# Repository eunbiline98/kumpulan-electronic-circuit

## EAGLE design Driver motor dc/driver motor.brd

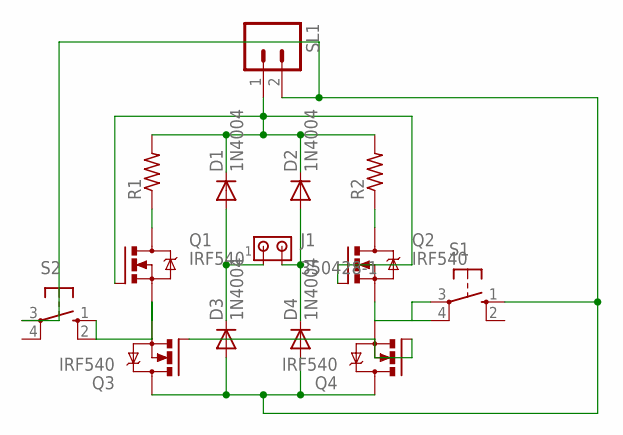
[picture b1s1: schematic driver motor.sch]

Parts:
D1, D2, D3, D4: 1N4004; DO41-10
J1: 350428-1
Q1, Q2, Q3, Q4: IRF540; TO220BV
R1, R2: R-US_0207/7; 0207/7
S1, S2: 10-XX; B3F-10XX
SL1: M02; 02P

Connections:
unnamed: D1.C, D2.C, Q1.G, Q2.G, R1.2, R2.2, SL1.1
unnamed: D1.A, D3.C, J1.1
unnamed: D2.A, D4.C, J1.2
unnamed: D3.A, D4.A, Q3.D, Q4.D, S1.1 (S), S2.3, SL1.2
unnamed: Q3.G, Q4.G
unnamed: Q2.S, Q4.S, S1.3, S1.4 (P1)
unnamed: Q1.D, R1.1
unnamed: Q2.D, R2.1
unnamed: Q1.S, Q3.S, S2.1 (S), S2.2 (S1)

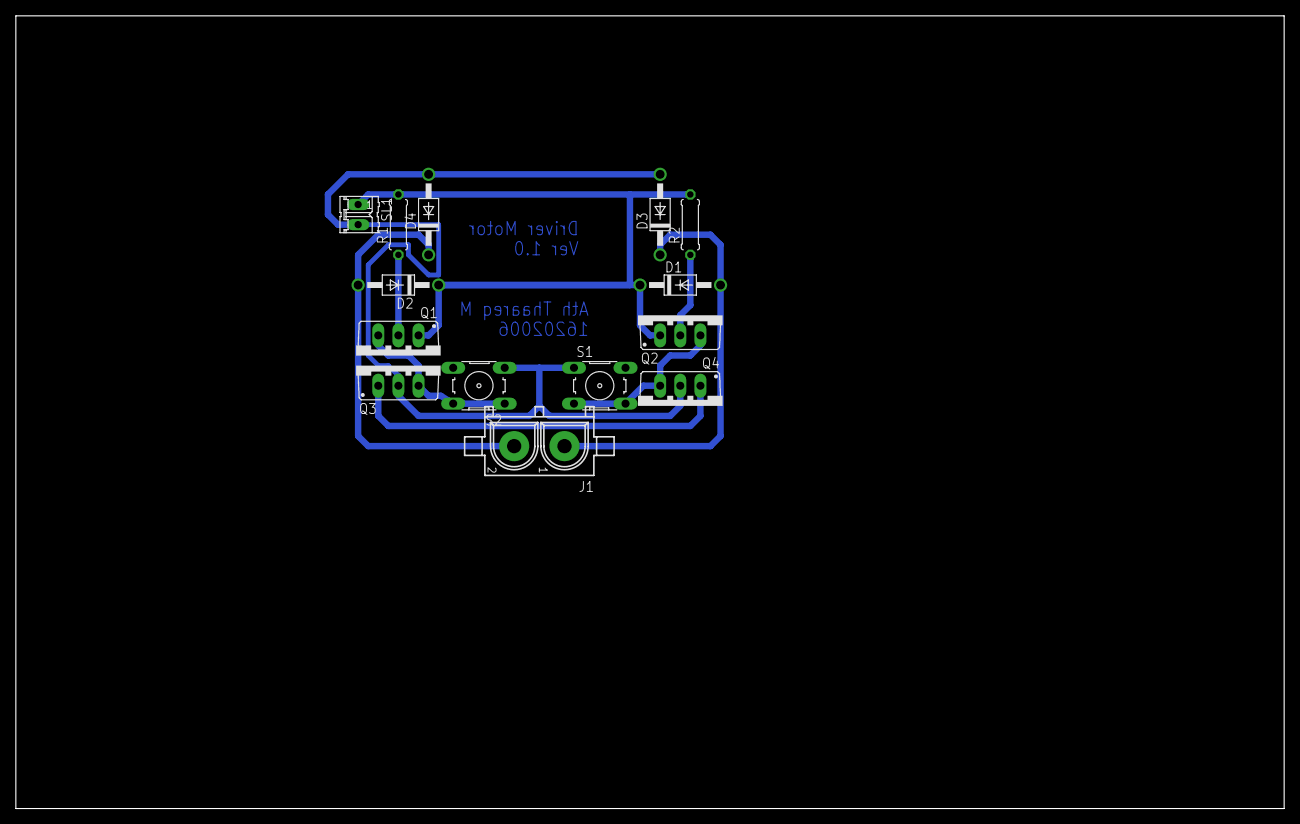
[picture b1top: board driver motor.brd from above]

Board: 2 copper layers, 160.0 x 100.0 mm, 14 parts (0 on the bottom side), 9 nets.

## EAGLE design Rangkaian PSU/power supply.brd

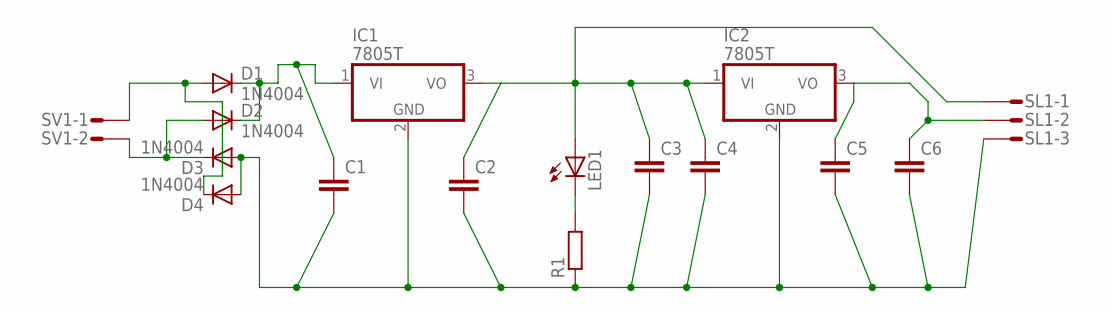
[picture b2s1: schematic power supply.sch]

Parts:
C1, C2, C3, C4, C5, C6: C5/5.5; C5B5.5
D1, D2, D3, D4: 1N4004; DO41-10
IC1, IC2: 7805T; TO220H
LED1: LED5MM
R1: R-EU_0207/7; 0207/7
SL1: M03S; 03P
SV1: L02P

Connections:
unnamed: C1.1, D1.C, D2.C, IC1.1 (VI)
unnamed: C1.2, C2.2, C3.2, C4.2, C5.2, C6.2, D3.A, D4.A, IC1.2 (GND), IC2.2 (GND), R1.1, SL1.3
unnamed: D2.A, D3.C, SV1.2
unnamed: D1.A, D4.C, SV1.1
unnamed: C2.1, C3.1, C4.1, IC1.3 (VO), IC2.1 (VI), LED1.A, SL1.1
unnamed: LED1.K (C), R1.2
unnamed: C5.1, C6.1, IC2.3 (VO), SL1.2

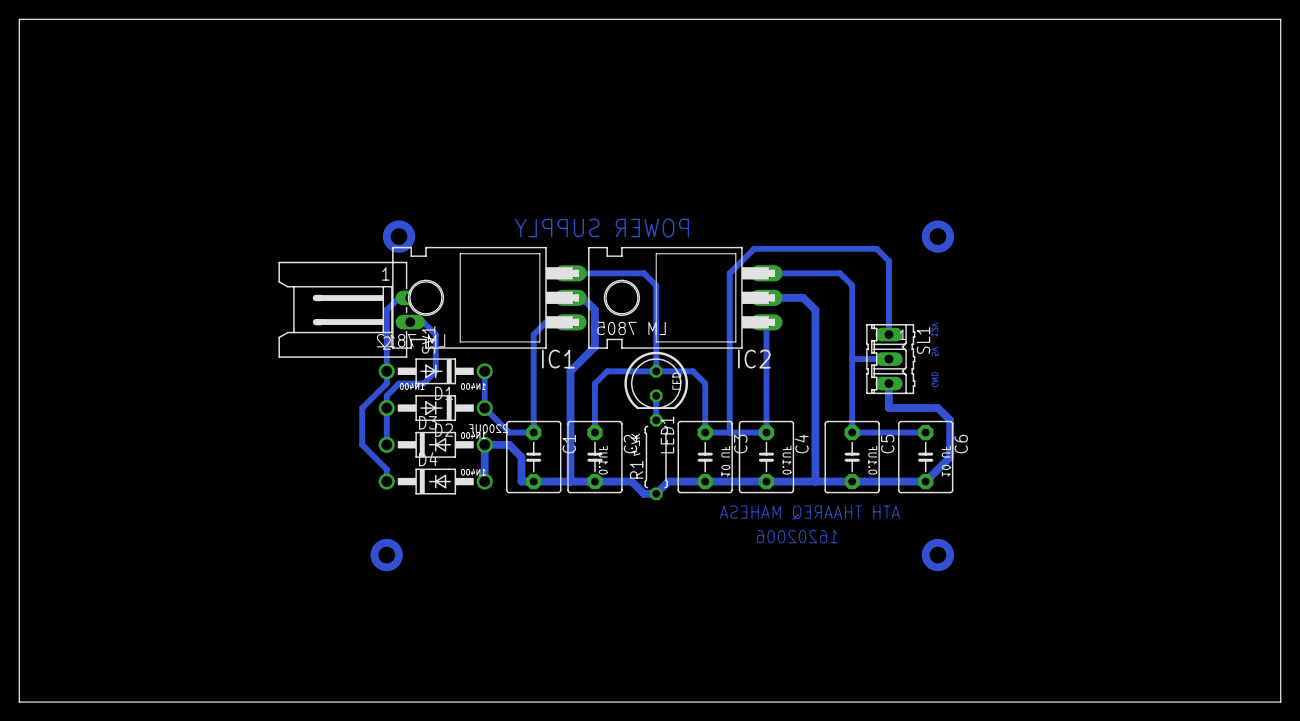
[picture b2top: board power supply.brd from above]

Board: 2 copper layers, 130.8 x 70.8 mm, 16 parts (0 on the bottom side), 7 nets.

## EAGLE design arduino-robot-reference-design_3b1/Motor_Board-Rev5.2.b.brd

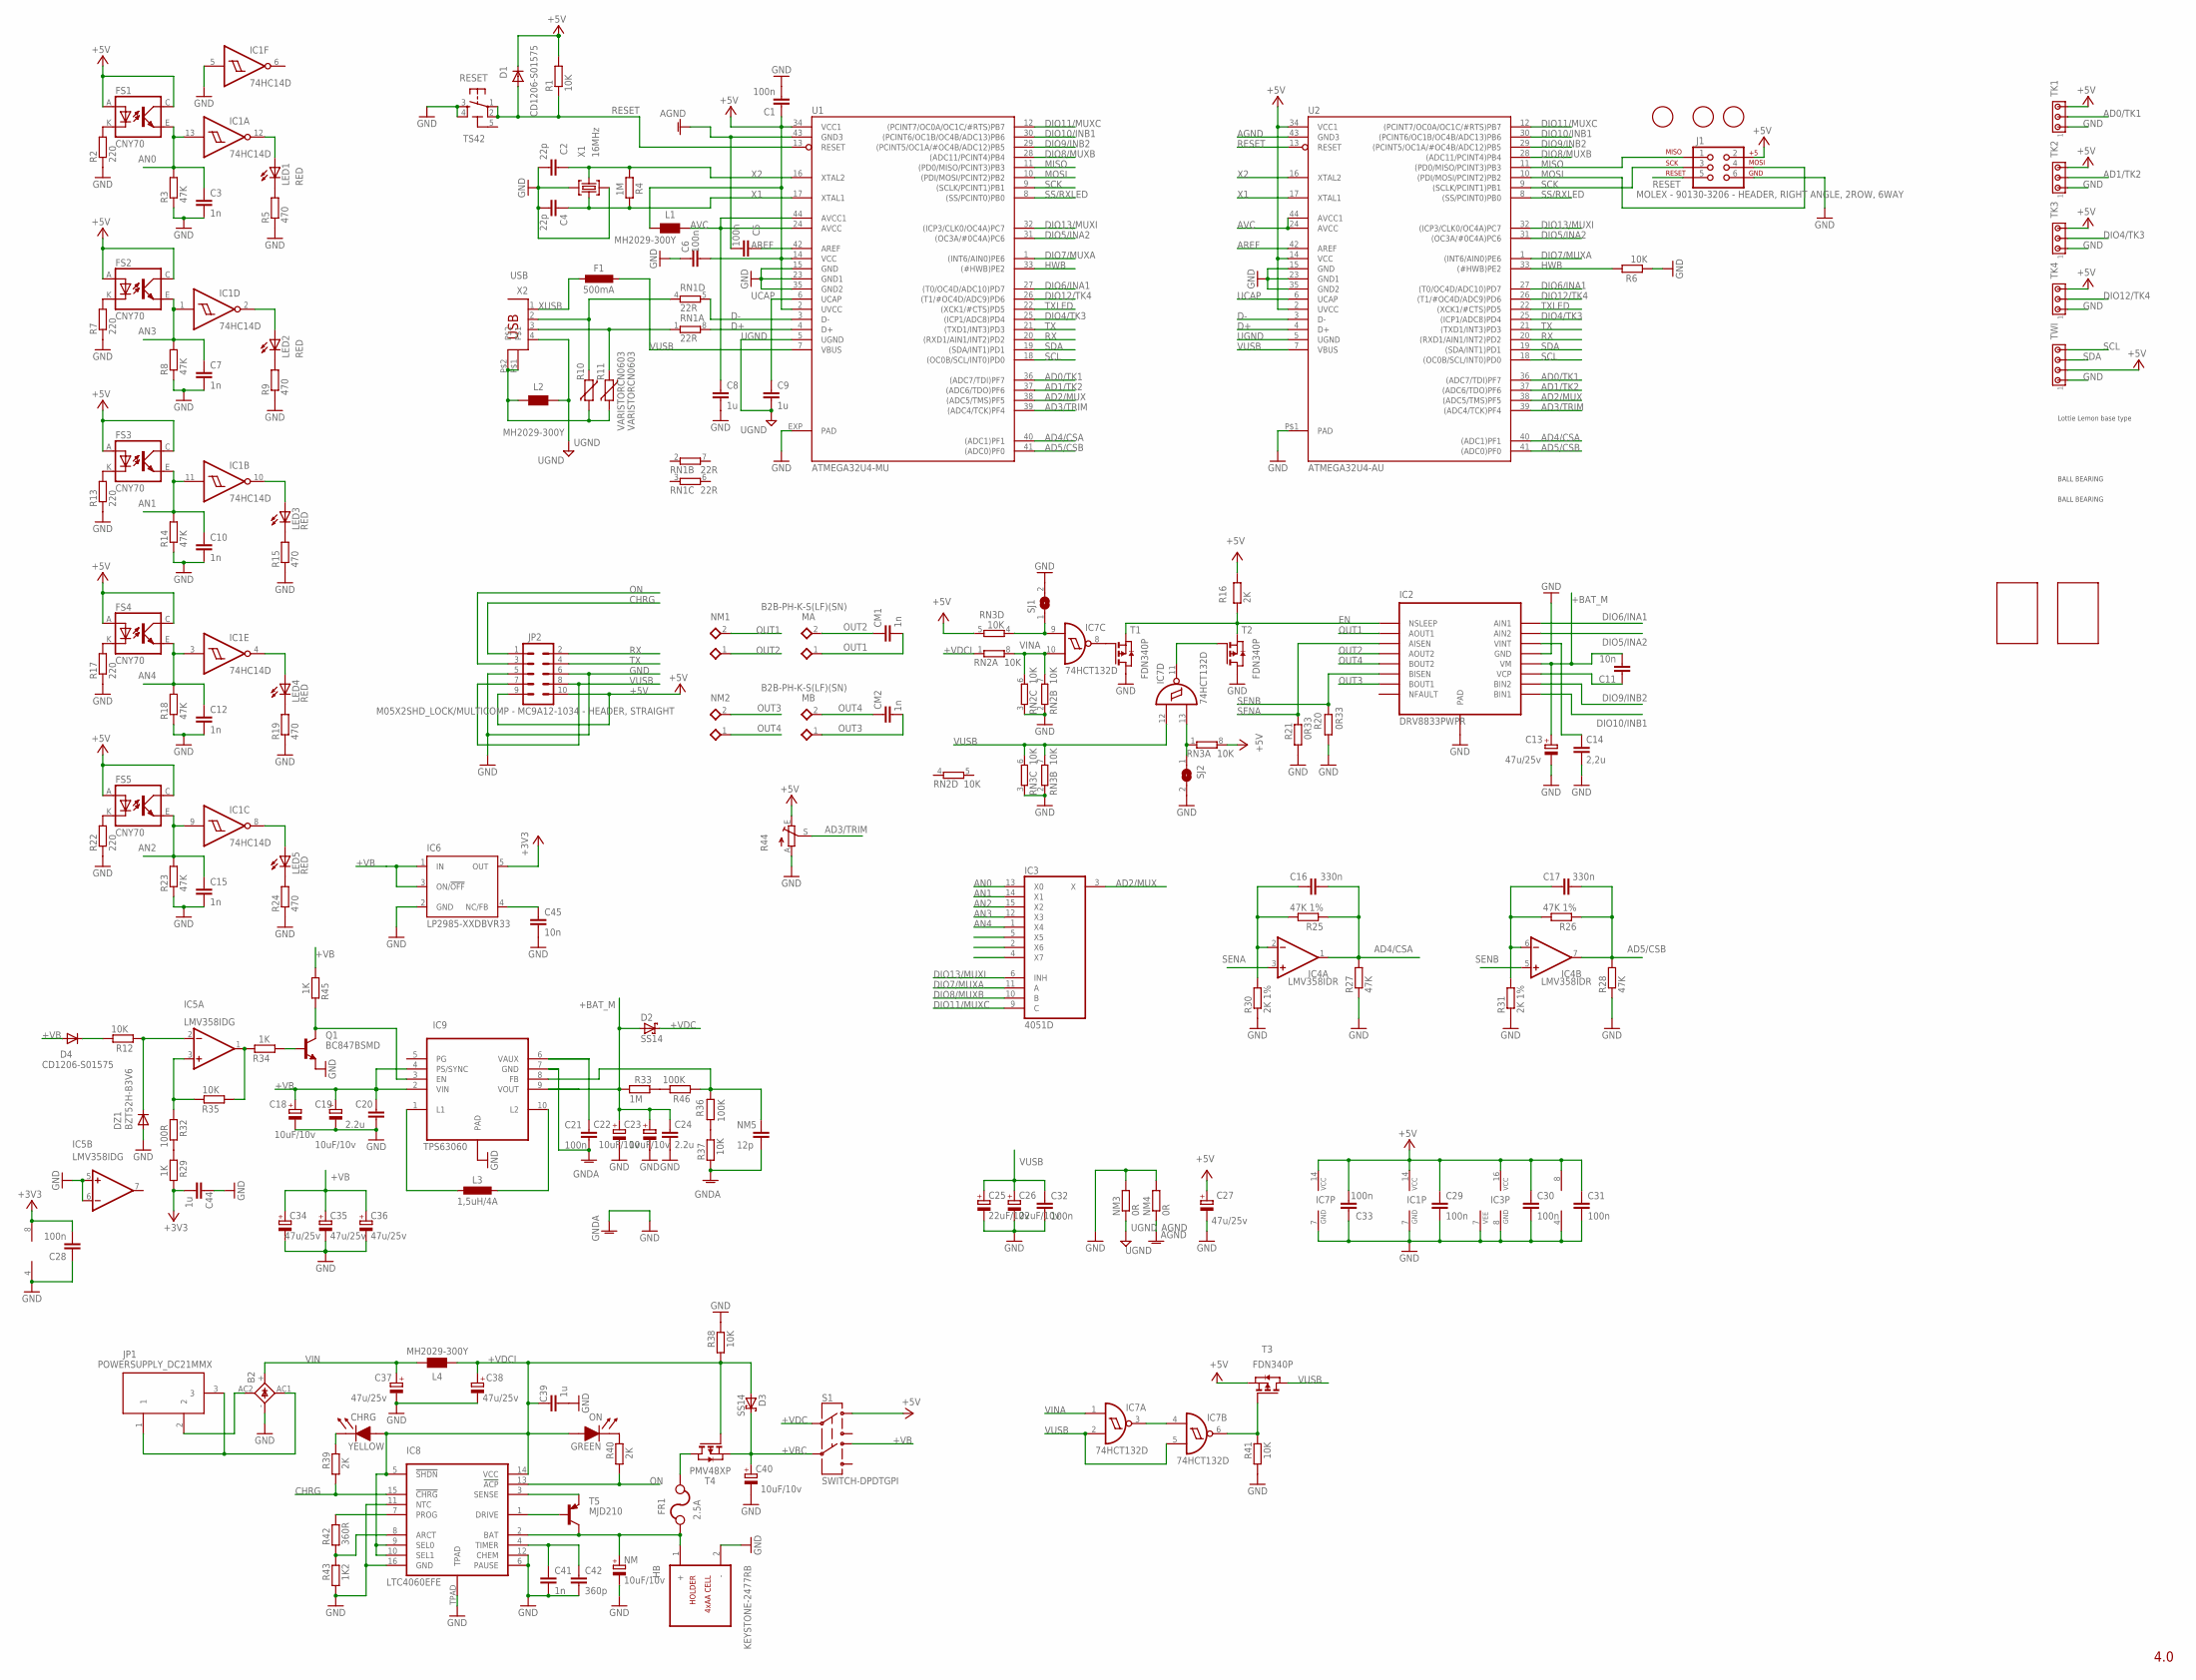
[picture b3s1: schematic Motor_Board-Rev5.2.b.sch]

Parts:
B2: KBL
BB1, BB2: LOTTIE_LEMON_BALL_BEARING; BALL_BEARING_LOTTIE_LEMON
C1, C5, C6, C21, C28, C29, C30, C31, C32, C33: 100n; C0603-ROUND
C2, C4: 22p; C0603-ROUND
C3, C7, C10, C12, C15, C41: 1n; C0603-ROUND
C8, C9, C39, C44: 1u; C0603-ROUND
C11, C45: 10n; C0603-ROUND
C13, C27, C34, C35, C36, C37, C38: 47u/25v; PANASONIC_D
C14: 2,2u; C0805K
C16, C17: 330n; C0603-ROUND
C18, C19, C22, C23, C40: 10uF/10v; SMC_B
C20, C24: 2.2u; C0805K
C25, C26: 22uF/10v; SMC_B
C42: 360p; C0603-ROUND
CHRG: YELLOW; SMD_LED0805
CM1, CM2: 1n; C0603-ROUND
D1, D4: CD1206-S01575; MINIMELF
D2, D3: SS14; SMB
DZ1: BZT52H-B3V6; SOD123
F1: 500mA; L1812
FM1, FM2, FM3: FIDUCIALMOUNT; FIDUCIA-MOUNT
FR1: 2.5A; MF-MSMF-S2
FS1, FS2, FS3, FS4, FS5: CNY70; 4
HB: KEYSTONE-2477RB; 4XAA_BATTERY-HOLDER
IC1: 74HC14D; SO14
IC2: DRV8833PWPR; R-PDSO-G16
IC3: 4051D; SO16
IC4: LMV358IDR; SO08@1
IC5: LMV358IDG; SO08
IC6: LP2985-XXDBVR33; SOT23-DBV
IC7: 74HCT132D; SO14
IC8: LTC4060EFE; TSSOP16
IC9: TPS63060; R-PVSON-10N
J1: MOLEX - 90130-3206 - HEADER, RIGHT ANGLE, 2ROW, 6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; 2X3
JP1: POWERSUPPLY_DC21MMX; POWERSUPPLY_DC-21MM
JP2: M05X2SHD_LOCK/MULTICOMP - MC9A12-1034 - HEADER, S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; 2X5-SHROUDED_LOCK
L1, L2, L4: MH2029-300Y; 0805
L3: 1,5uH/4A; POWER-CHOKE_WE-TPC
LED1, LED2, LED3, LED4, LED5: RED; CHIP-LED0805
LL1: LOTTIE_LEMON_DC_MOTOR_48X_L; CARCASA_MOTOR_L_LOTTIE_LEMON
MA: B2B-PH-K-S(LF)(SN); B2B-PH_KL
MB: B2B-PH-K-S(LF)(SN); B2B-PH_KL
NM: 10uF/10v; SMC_B
NM1, NM2: B2B-PH-K-S(LF)(SN); B2B-PH_KL
NM3, NM4: 0R; R0805
NM5: 12p; C0603-ROUND
ON: GREEN; SMD_LED0805
Q1: BC847BSMD; SOT23
R1, R6, R12, R35, R37, R38, R41: 10K; R0603-ROUND
R2, R7, R13, R17, R22: 220; R0603-ROUND
R3, R8, R14, R18, R23, R27, R28: 47K; R0603-ROUND
R4, R33: 1M; R0603-ROUND
R5, R9, R15, R19, R24: 470; R0603-ROUND
R10, R11: VARISTORCN0603; CT/CN0603
R16, R39, R40: 2K; R0603-ROUND
R20, R21: 0R33; R1206
R25, R26: 47K 1%; R0603-ROUND
R29, R34, R45: 1K; R0603-ROUND
R30, R31: 2K 1%; R0603-ROUND
R32: 100R; R0603-ROUND
R36, R46: 100K; R0603-ROUND
R42: 360R; R0603-ROUND
R43: 1K2; R0603-ROUND
R44: TRIM_EU-CA9V; CA9V
RESET: TS42
RN1: 22R; CAY16
RN2, RN3: 10K; CAY16
RR1: LOTTIE_LEMON_DC_MOTOR_48X_R; CARCASA_MOTOR_R_LOTTIE_LEMON
S1: SWITCH-DPDTGPI; GPI-152-3013
SJ1, SJ2: SJL
T1, T2, T3: FDN340P; SOT-23
T4: PMV48XP; SOT-23
T5: MJD210; DPAK
TK1, TK2, TK3, TK4: MTA03-100; 10X03MTA
TWI: MTA04-100; 10X04MTA
U1: ATMEGA32U4-MU; QFN44ML7X7
U2: ATMEGA32U4-AU; TQFP44-PAD
U$1: LOTTIE_LEMON_BASE_TYPE; BASE_ROBOT_001
U$2: LOTTIE_LEMON_PADS; PADS_LOTTIE_LEMON
W1, W2: LOTTIE_LEMON_WHEEL; WHEEL_LOTTIE_LEMON
X1: 16MHz; CRYSTAL-3.2-2.5
X2: USB; PN61729

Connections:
5-GND: RESET.5 (5-GND)
+3V3: C28.2, C44.1, IC5.8 (V+), IC6.5 (OUT), R29.2
+5V: C1.1, C6.2, C27.+, C29.1, C30.1, C31.1, C33.2, D1.C, FS1.A, FS1.C (COL), FS2.A, FS2.C (COL), FS3.A, FS3.C (COL), FS4.A, FS4.C (COL), FS5.A, FS5.C (COL), IC1.14 (VCC), IC3.16 (VCC), IC4.8 (V+), IC7.14 (VCC), J1.2, JP2.9, JP2.10, L1.1, R1.2, R16.2, R44.E, RN3.5 (2), RN3.8 (2), S1.10 (1), T3.2 (S), TK1.3, TK2.3, TK3.3, TK4.3, TWI.2, U1.2 (UVCC), U1.14 (VCC), U1.34 (VCC1), U2.2 (UVCC), U2.14 (VCC), U2.34 (VCC1)
+BAT_M: C11.2, C13.+, C22.+, C23.+, C24.1, D2.A, IC2.P$12 (VM), IC9.9 (VOUT), R33.1
+VB: C18.+, C19.+, C20.1, C34.+, C35.+, C36.+, D4.A, IC6.1 (IN), IC6.3 (ON/!OFF), IC9.2 (VIN), IC9.4 (PS/SYNC), R45.1, S1.11 (4)
+VBC: C40.+, D3.C, S1.C@2 (5), T4.2 (S)
+VDC: D2.C, S1.C@1 (2)
+VDCI: C38.+, C39.2, CHRG.2 (AN), D3.A, IC8.5 (!SHDN), IC8.9 (SEL0), IC8.10 (SEL1), IC8.14 (VCC), L4.2, ON.2 (AN), R38.1, RN2.1, T4.3 (G)
AD0/TK1: TK1.2, U1.36 ((ADC7/TDI)PF7), U2.36 ((ADC7/TDI)PF7)
AD1/TK2: TK2.2, U1.37 ((ADC6/TDO)PF6), U2.37 ((ADC6/TDO)PF6)
AD2/MUX: IC3.3 (X), U1.38 ((ADC5/TMS)PF5), U2.38 ((ADC5/TMS)PF5)
AD3/TRIM: R44.S, U1.39 ((ADC4/TCK)PF4), U2.39 ((ADC4/TCK)PF4)
AD4/CSA: C16.2, IC4.1 (OUT), R25.1, R27.2, U1.40 ((ADC1)PF1), U2.40 ((ADC1)PF1)
AD5/CSB: C17.2, IC4.7 (OUT), R26.1, R28.2, U1.41 ((ADC0)PF0), U2.41 ((ADC0)PF0)
AGND: C5.2, NM4.1, U1.43 (GND3), U2.43 (GND3)
AN0: C3.1, FS1.E (EMI), IC1.13 (I), IC3.13 (X0), R3.2
AN1: C10.1, FS3.E (EMI), IC1.11 (I), IC3.14 (X1), R14.2
AN2: C15.1, FS5.E (EMI), IC1.9 (I), IC3.15 (X2), R23.2
AN3: C7.1, FS2.E (EMI), IC1.1 (I), IC3.12 (X3), R8.2
AN4: C12.1, FS4.E (EMI), IC1.3 (I), IC3.1 (X4), R18.2
AREF: C5.1, U1.42 (AREF), U2.42 (AREF)
AVC: C8.1, L1.2, U1.24 (AVCC), U1.44 (AVCC1), U2.24 (AVCC), U2.44 (AVCC1)
CHRG: IC8.15 (!CHRG), JP2.1, R39.1
D+: RN1.8 (2), U1.4 (D+), U2.4 (D+)
D-: RN1.5 (2), U1.3 (D-), U2.3 (D-)
DIO4/TK3: TK3.2, U1.25 ((ICP1/ADC8)PD4), U2.25 ((ICP1/ADC8)PD4)
DIO5/INA2: IC2.P$15 (AIN2), U1.31 ((OC3A/#0C4A)PC6), U2.31 ((OC3A/#0C4A)PC6)
DIO6/INA1: IC2.P$16 (AIN1), U1.27 ((T0/OC4D/ADC10)PD7), U2.27 ((T0/OC4D/ADC10)PD7)
DIO7/MUXA: IC3.11 (A), U1.1 ((INT6/AIN0)PE6), U2.1 ((INT6/AIN0)PE6)
DIO8/MUXB: IC3.10 (B), U1.28 ((ADC11/PCINT4)PB4), U2.28 ((ADC11/PCINT4)PB4)
DIO9/INB2: IC2.P$10 (BIN2), U1.29 ((PCINT5/OC1A/#OC4B/ADC12)PB5), U2.29 ((PCINT5/OC1A/#OC4B/ADC12)PB5)
DIO10/INB1: IC2.P$9 (BIN1), U1.30 ((PCINT6/OC1B/OC4B/ADC13)PB6), U2.30 ((PCINT6/OC1B/OC4B/ADC13)PB6)
DIO11/MUXC: IC3.9 (C), U1.12 ((PCINT7/OC0A/OC1C/#RTS)PB7), U2.12 ((PCINT7/OC0A/OC1C/#RTS)PB7)
DIO12/TK4: TK4.2, U1.26 ((T1/#OC4D/ADC9)PD6), U2.26 ((T1/#OC4D/ADC9)PD6)
DIO13/MUXI: IC3.6 (INH), U1.32 ((ICP3/CLK0/OC4A)PC7), U2.32 ((ICP3/CLK0/OC4A)PC7)
EN: IC2.P$1 (NSLEEP), R16.1, T1.2 (S), T2.2 (S)
GND: B2.-, C1.2, C2.2, C3.2, C4.2, C6.1, C7.2, C8.2, C10.2, C12.2, C13.-, C14.2, C15.2, C18.-, C19.-, C20.2, C22.-, C23.-, C24.2, C25.-, C26.-, C27.-, C28.1, C29.2, C30.2, C31.2, C32.1, C33.1, C34.-, C35.-, C36.-, C37.-, C38.-, C39.1, C40.-, C41.2, C42.2, C44.2, C45.2, DZ1.A, HB.2 (-), IC1.5 (I), IC1.7 (GND), IC2.P$13 (GND), IC2.P$17 (PAD), IC3.7 (VEE), IC3.8 (GND), IC4.4 (V-), IC5.4 (V-), IC5.5 (+IN), IC5.6 (-IN), IC6.2 (GND), IC7.7 (GND), IC8.6 (PAUSE), IC8.11 (NTC), IC8.12 (CHEM), IC8.16 (GND), IC8.TPAD, IC9.PAD, J1.6, JP2.5, JP2.6, NM.-, NM3.2, NM4.2, Q1.2 (E), R2.1, R3.1, R5.1, R6.1, R7.1, R8.1, R9.1, R13.1, R14.1, R15.1, R17.1, R18.1, R19.1, R20.1, R21.1, R22.1, R23.1, R24.1, R27.1, R28.1, R30.1, R31.1, R38.2, R41.1, R43.1, R44.A, RESET.3, RESET.4, RN2.2 (1), RN2.3 (1), RN3.2 (1), RN3.3 (1), SJ1.2, SJ2.2, T1.1 (D), T2.1 (D), TK1.1, TK2.1, TK3.1, TK4.1, TWI.1, U1.15 (GND), U1.23 (GND1), U1.35 (GND2), U1.EXP (PAD), U2.15 (GND), U2.23 (GND1), U2.35 (GND2), U2.P$1 (PAD), X1.2 (GND), X1.4 (GND)
GNDA: C21.2, IC9.7 (GND), NM5.2, R37.1
HWB: R6.2, U1.33 ((#HWB)PE2), U2.33 ((#HWB)PE2)
MISO: J1.1, U1.11 ((PD0/MISO/PCINT3)PB3), U2.11 ((PD0/MISO/PCINT3)PB3)
MOSI: J1.4, U1.10 ((PDI/MOSI/PCINT2)PB2), U2.10 ((PDI/MOSI/PCINT2)PB2)
unnamed: CHRG.1 (CA), R39.2
unnamed: IC7.3 (O), IC7.4 (I0)
unnamed: B2.AC2 (AC1), JP1.2
unnamed: IC1.12 (O), LED1.A
unnamed: IC1.10 (O), LED3.A
unnamed: B2.AC1 (AC2), JP1.1, JP1.3
unnamed: L2.1, R10.2, R11.2, X2.P$1, X2.P$2
unnamed: IC7.13 (I1), RN3.1, SJ2.1
unnamed: IC9.10 (L2), L3.2
unnamed: IC8.8 (ARCT), R42.1, R43.2
unnamed: FS1.K (C), R2.2
unnamed: FS3.K (C), R13.2
unnamed: LED1.C, R5.2
unnamed: IC8.7 (PROG), R42.2
unnamed: LED3.C, R15.2
unnamed: FS5.K (C), R22.2
unnamed: FS2.K (C), R7.2
unnamed: IC7.6 (O), R41.2, T3.3 (G)
unnamed: LED5.C, R24.2
unnamed: C11.1, IC2.P$11 (VCP)
unnamed: FS4.K (C), R17.2
unnamed: LED4.C, R19.2
unnamed: LED2.C, R9.2
unnamed: IC8.3 (SENSE), T5.3 (E)
unnamed: C17.1, IC4.6 (-IN), R26.2, R31.2
unnamed: C16.1, IC4.2 (-IN), R25.2, R30.2
unnamed: IC7.8 (O), T1.3 (G)
unnamed: IC8.1 (DRIVE), T5.1 (B)
unnamed: ON.1 (CA), R40.2
unnamed: FR1.P$1, HB.1 (+), IC8.2 (BAT), NM.+, T5.4 (C)
unnamed: C41.1, C42.1, IC8.4 (TIMER)
unnamed: C21.1, IC9.6 (VAUX)
unnamed: IC1.8 (O), LED5.A
unnamed: IC1.2 (O), LED2.A
unnamed: IC1.4 (O), LED4.A
unnamed: IC9.8 (FB), NM5.1, R36.1, R46.1
unnamed: IC7.11 (O), T2.3 (G)
unnamed: C45.1, IC6.4 (NC/FB)
unnamed: C14.1, IC2.P$14 (VINT)
unnamed: R36.2, R37.2
unnamed: IC7.9 (I0), RN3.4 (1), SJ1.1
unnamed: IC5.3 (+IN), R32.1, R35.2
unnamed: FR1.P$2, T4.1 (D)
unnamed: IC9.1 (L1), L3.1
unnamed: DZ1.C, IC5.2 (-IN), R12.1
unnamed: R29.1, R32.2
unnamed: IC9.3 (EN), Q1.3 (C), R45.2
unnamed: R11.1, RN1.1, X2.3
unnamed: IC5.1 (OUT), R34.2, R35.1
unnamed: Q1.1 (B), R34.1
unnamed: R10.1, RN1.4 (1), X2.2
unnamed: D4.C, R12.2
unnamed: R33.2, R46.2
ON: IC8.13 (!ACP), JP2.3, R40.1
OUT1: CM1.2, IC2.P$2 (AOUT1), MA.1, NM1.2
OUT2: CM1.1, IC2.P$4 (AOUT2), MA.2, NM1.1
OUT3: CM2.1, IC2.P$7 (BOUT1), MB.1, NM2.2
OUT4: CM2.2, IC2.P$5 (BOUT2), MB.2, NM2.1
RESET: D1.A, J1.5, R1.1, RESET.1, RESET.2, U1.13 (RESET), U2.13 (RESET)
RX: JP2.2, U1.20 ((RXD1/AIN1/INT2)PD2), U2.20 ((RXD1/AIN1/INT2)PD2)
SCK: J1.3, U1.9 ((SCLK/PCINT1)PB1), U2.9 ((SCLK/PCINT1)PB1)
SCL: TWI.4, U1.18 ((OC0B/SCL/INT0)PD0), U2.18 ((OC0B/SCL/INT0)PD0)
SDA: TWI.3, U1.19 ((SDA/INT1)PD1), U2.19 ((SDA/INT1)PD1)
SENA: IC2.P$3 (AISEN), IC4.3 (+IN), R21.2
SENB: IC2.P$6 (BISEN), IC4.5 (+IN), R20.2
SS/RXLED: U1.8 ((SS/PCINT0)PB0), U2.8 ((SS/PCINT0)PB0)
TX: JP2.4, U1.21 ((TXD1/INT3)PD3), U2.21 ((TXD1/INT3)PD3)
TXLED: U1.22 ((XCK1/#CTS)PD5), U2.22 ((XCK1/#CTS)PD5)
UCAP: C9.1, U1.6 (UCAP), U2.6 (UCAP)
UGND: C9.2, L2.2, NM3.1, U1.5 (UGND), U2.5 (UGND), X2.4
VIN: B2.+, C37.+, L4.1
VINA: IC7.1 (I0), IC7.10 (I1), RN2.6 (2), RN2.7 (2), RN2.8 (2)
VUSB: C25.+, C26.+, C32.2, F1.2, IC7.2 (I1), IC7.5 (I1), IC7.12 (I0), JP2.7, JP2.8, RN3.6 (2), RN3.7 (2), T3.1 (D), U1.7 (VBUS), U2.7 (VBUS)
X1: C4.1, R4.2, U1.17 (XTAL1), U2.17 (XTAL1), X1.1 (C1)
X2: C2.1, R4.1, U1.16 (XTAL2), U2.16 (XTAL2), X1.3 (C2)
XUSB: F1.1, X2.1

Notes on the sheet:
4.0

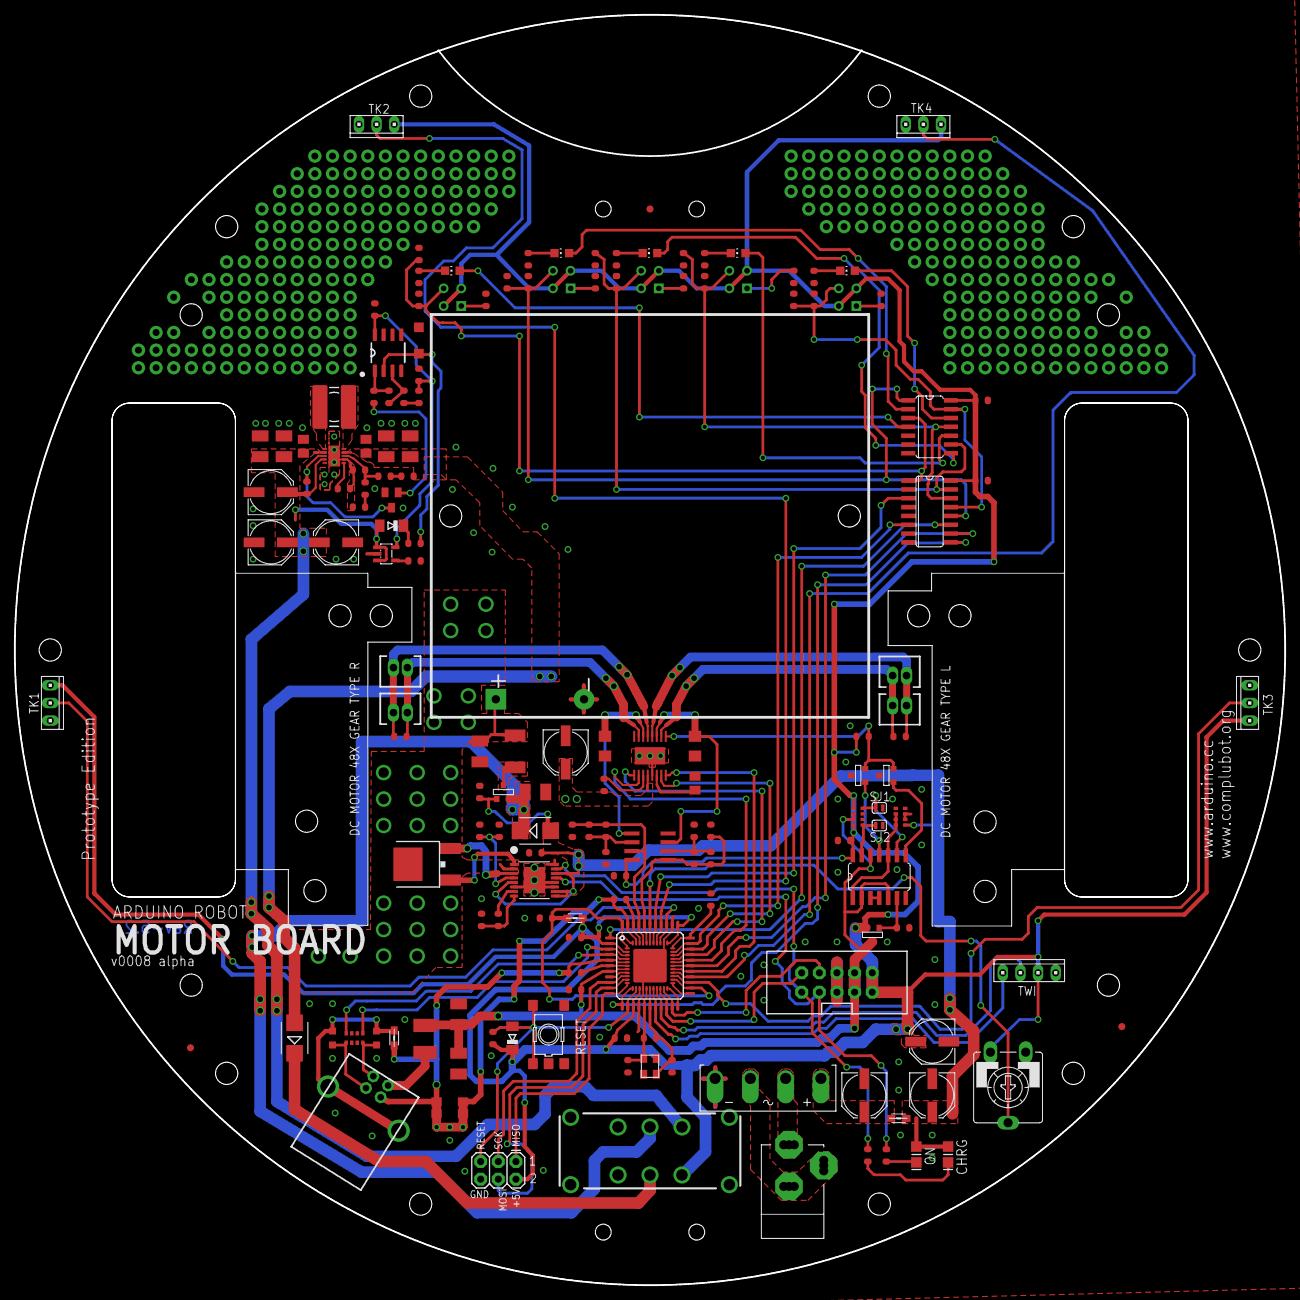
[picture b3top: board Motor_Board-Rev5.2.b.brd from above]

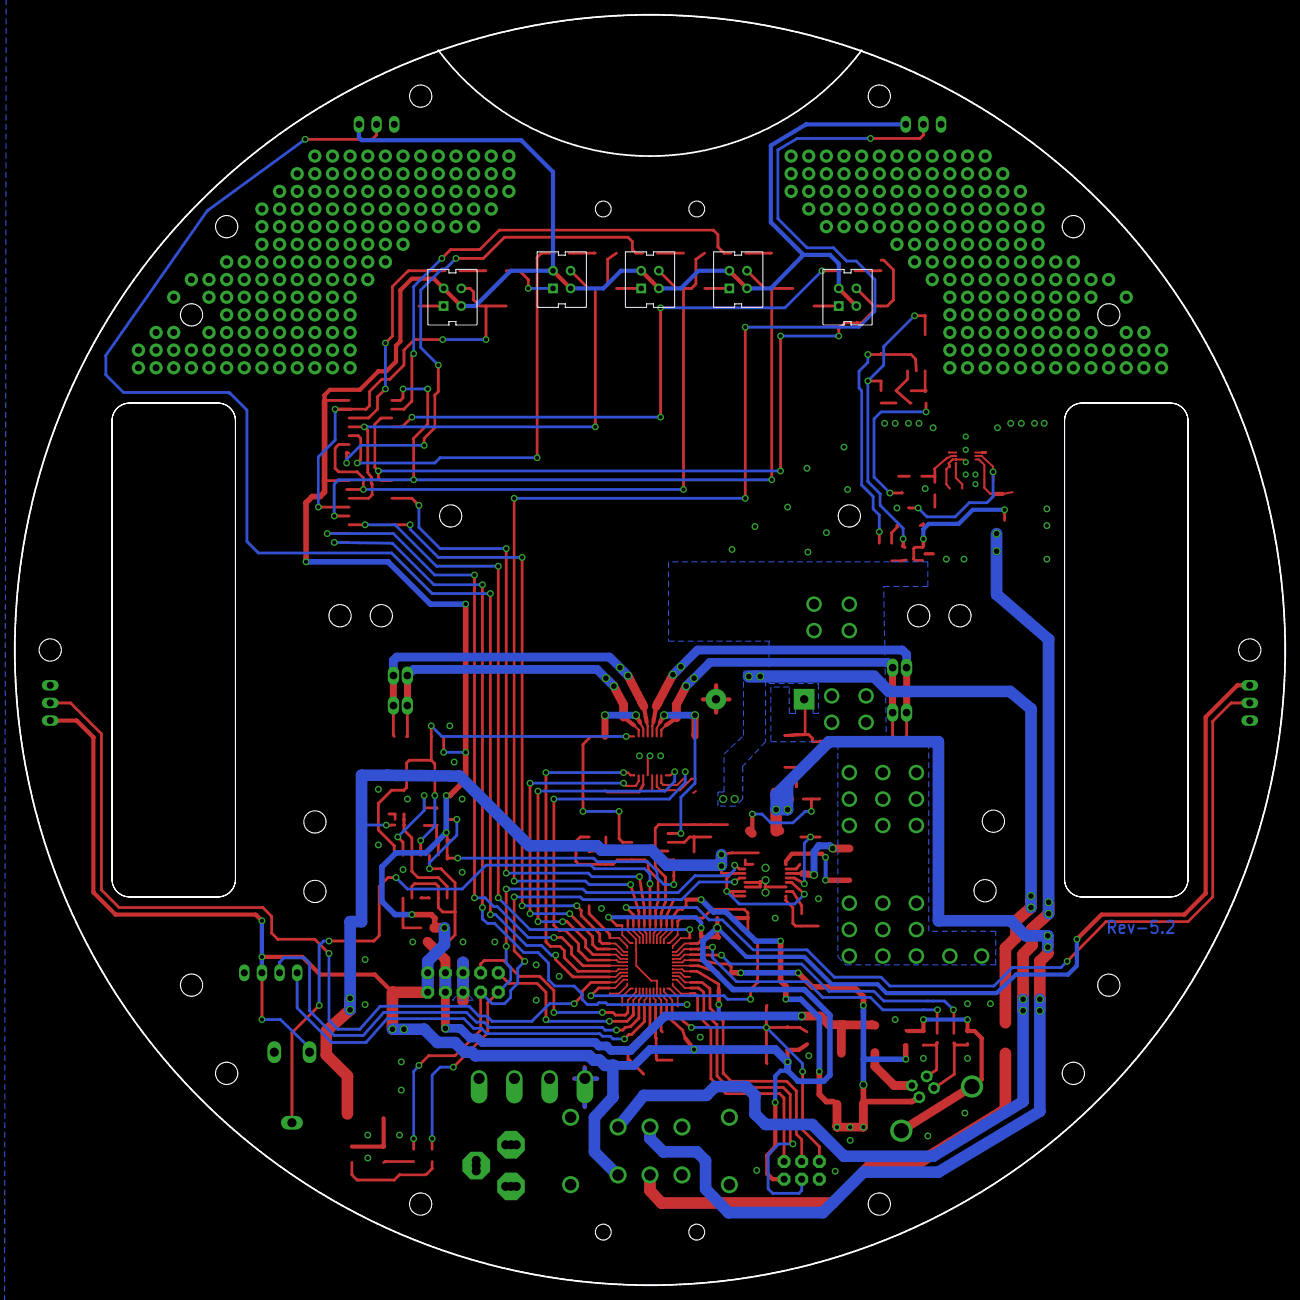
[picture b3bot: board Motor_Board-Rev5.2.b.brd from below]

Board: 2 copper layers, 182.9 x 182.9 mm, 170 parts (5 on the bottom side), 116 nets.

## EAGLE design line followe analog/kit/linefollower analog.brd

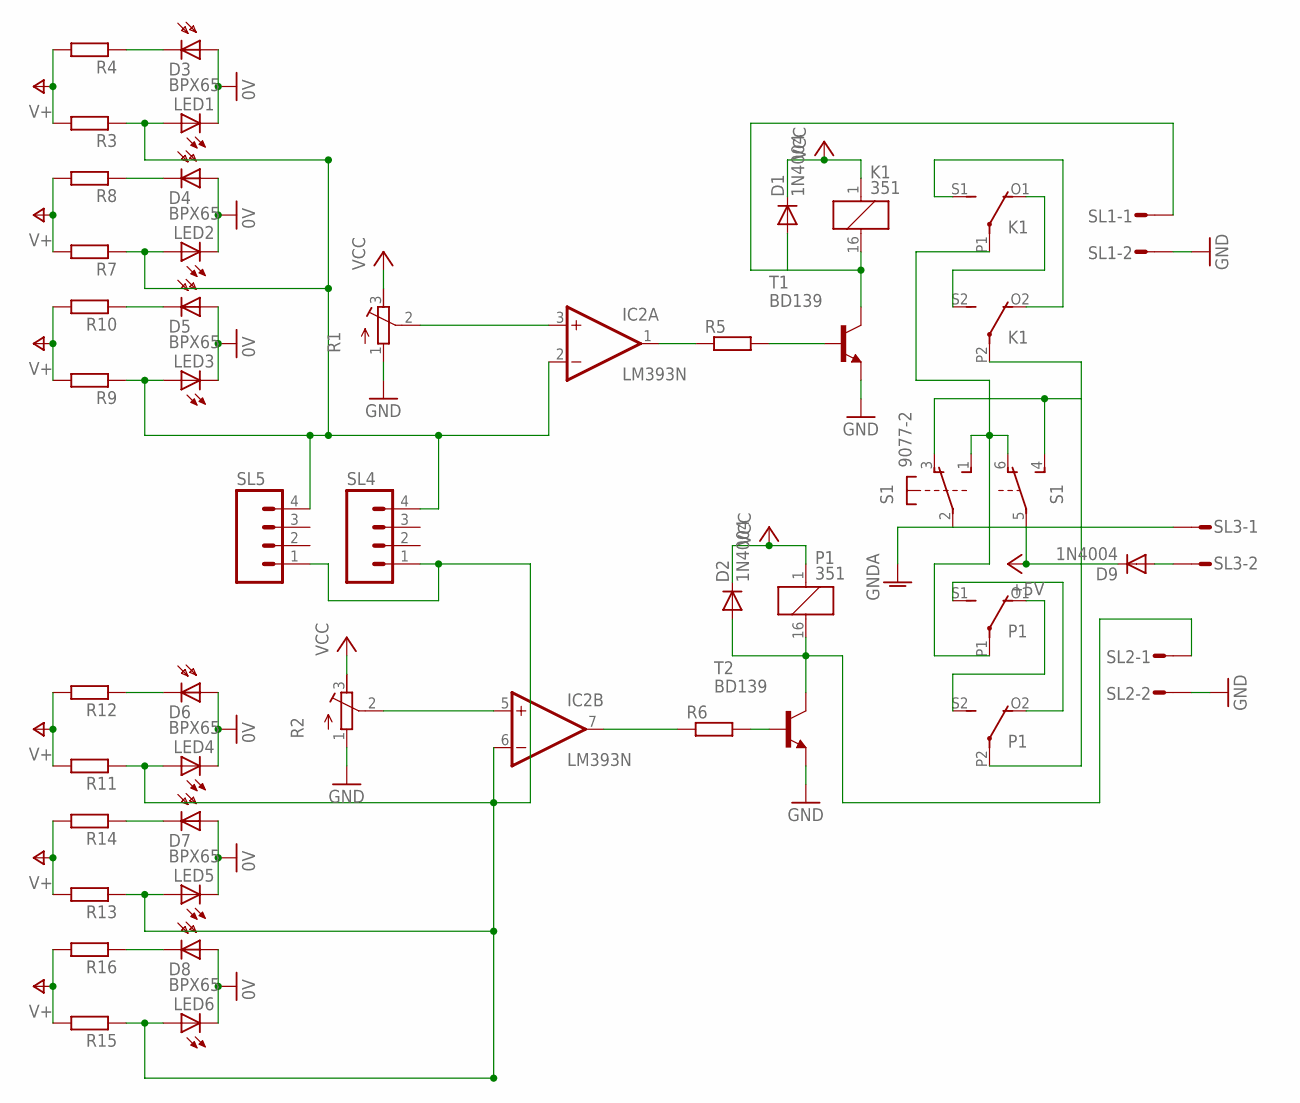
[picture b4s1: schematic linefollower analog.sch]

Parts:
D1, D2, D9: 1N4004; DO41-10
D3, D4, D5, D6, D7, D8: BPX65
IC2: LM393N; DIL08
K1: 351
LED1, LED2, LED3, LED4, LED5, LED6: LED5MM
P1: 351
R1, R2: R-TRIMM3339P; RTRIM3339P
R3, R4, R7, R8, R9, R10, R11, R12, R13, R14, R15, R16: R-EU_0204/7; 0204/7
R5, R6: R-EU_0207/7; 0207/7
S1: 9077-2
SL1, SL2, SL3: M02S; 02P
SL4, SL5: M04; 04P
T1, T2: BD139; TO126

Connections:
0V: D3.A, D4.A, D5.A, D6.A, D7.A, D8.A, LED1.K (C), LED2.K (C), LED3.K (C), LED4.K (C), LED5.K (C), LED6.K (C)
+5V: D9.C, S1.2, SL3.1
GND: IC2.4 (V-), R1.1 (E), R2.1 (E), SL1.2, SL2.2, T1.1 (E), T2.1 (E)
unnamed: IC2.3 (+IN), R1.2 (S)
unnamed: IC2.5 (+IN), R2.2 (S)
unnamed: IC2.7 (OUT), R6.1
unnamed: IC2.1 (OUT), R5.1
unnamed: R5.2, T1.3 (B)
unnamed: R6.2, T2.3 (B)
unnamed: IC2.6 (-IN), LED4.A, LED5.A, LED6.A, R11.1, R13.1, R15.1, SL4.1, SL5.1
unnamed: D1.A, K1.16 (2), SL1.1, T1.2 (C)
unnamed: D9.A, SL3.2
unnamed: K1.O2 (O), K1.S1 (S)
unnamed: K1.O1 (O), K1.S2 (S)
unnamed: K1.P1, P1.P1, S1.1 (S), S1.6 (O)
unnamed: K1.P2, P1.P2, S1.3 (O), S1.4 (S)
unnamed: P1.O2 (O), P1.S1 (S)
unnamed: P1.O1 (O), P1.S2 (S)
unnamed: D3.K (C), R4.1
unnamed: IC2.2 (-IN), LED1.A, LED2.A, LED3.A, R3.1, R7.1, R9.1, SL4.4, SL5.4
unnamed: D4.K (C), R8.1
unnamed: D5.K (C), R10.1
unnamed: D6.K (C), R12.1
unnamed: D7.K (C), R14.1
unnamed: D8.K (C), R16.1
P1: D2.A, P1.16 (2), SL2.1, T2.2 (C)
V+: R3.2, R4.2, R7.2, R8.2, R9.2, R10.2, R11.2, R12.2, R13.2, R14.2, R15.2, R16.2
VCC: D1.C, D2.C, IC2.8 (V+), K1.1, P1.1, R1.3 (A), R2.3 (A)

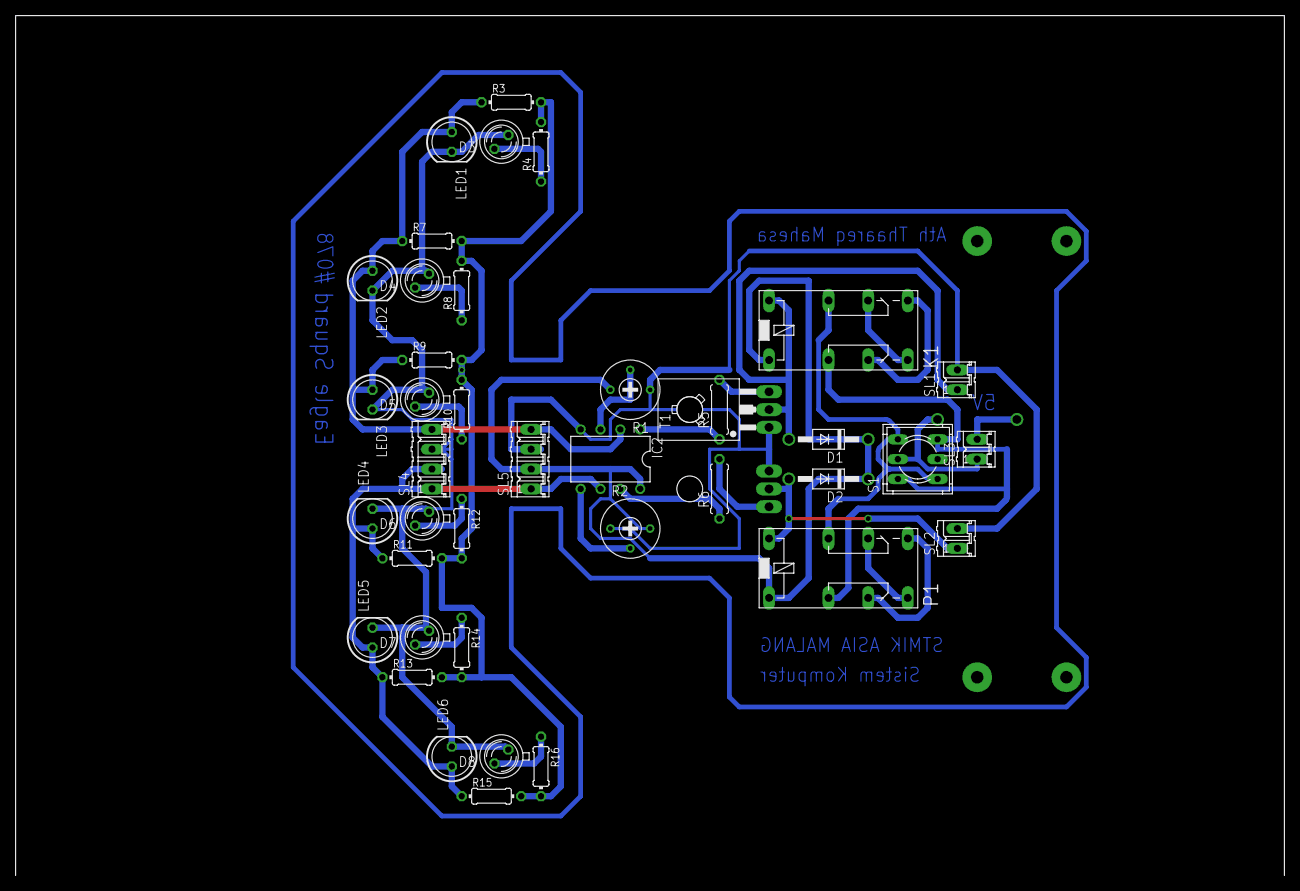
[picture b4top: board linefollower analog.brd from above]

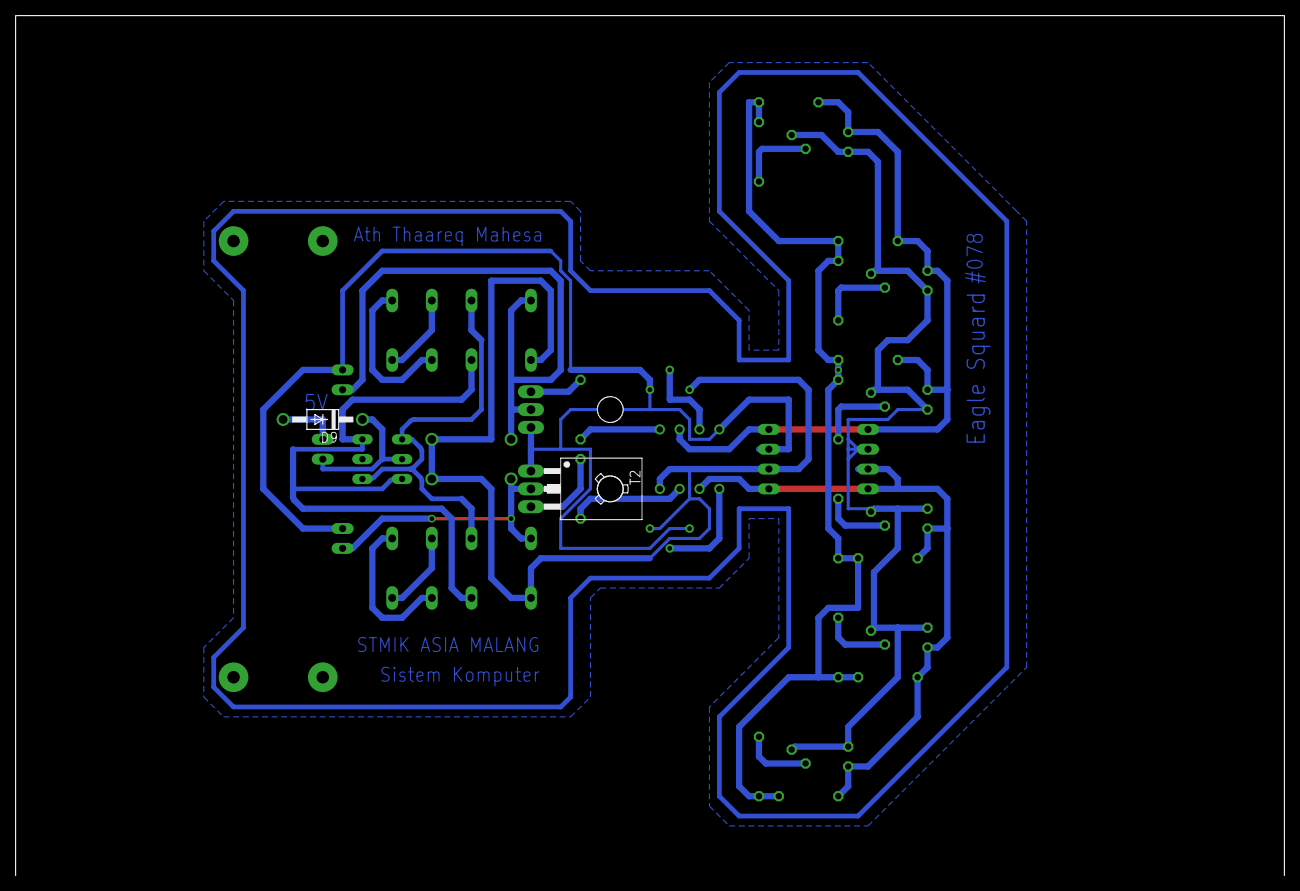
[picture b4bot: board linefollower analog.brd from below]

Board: 2 copper layers, 162.5 x 110.2 mm, 42 parts (2 on the bottom side), 28 nets.

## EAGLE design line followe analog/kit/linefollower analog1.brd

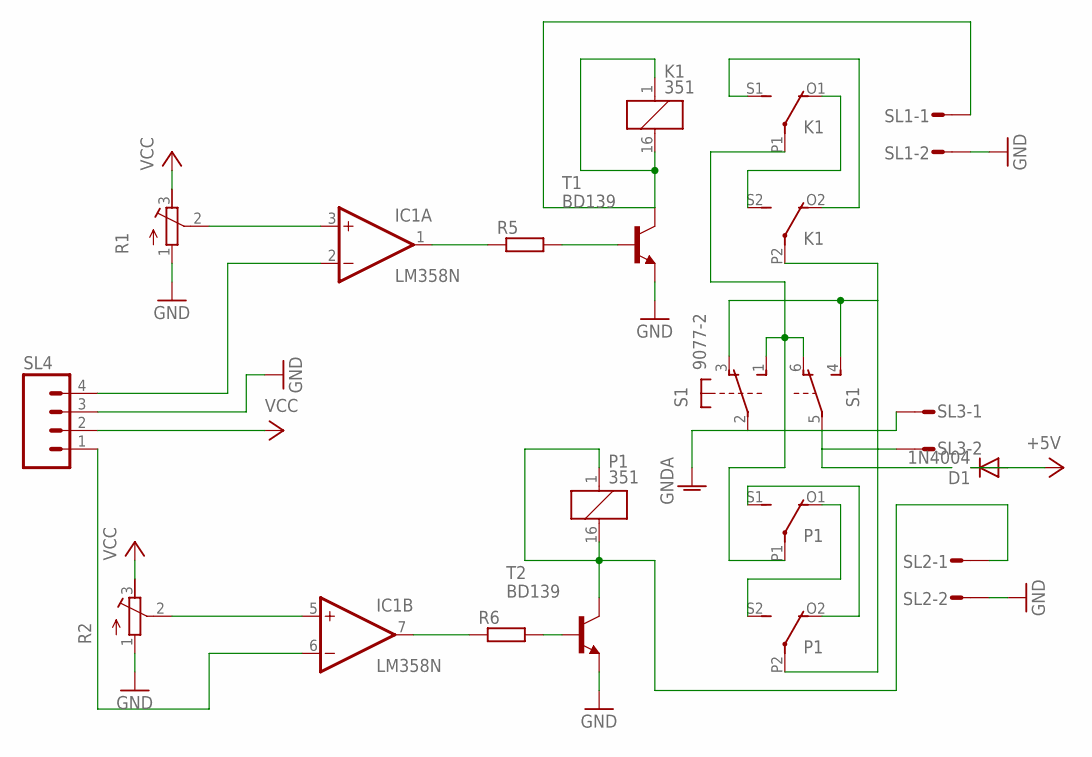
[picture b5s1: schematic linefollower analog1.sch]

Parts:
D1: 1N4004; DO41-10
IC1: LM358N; DIL08
K1: 351
P1: 351
R1, R2: R-TRIMM3339P; RTRIM3339P
R5, R6: R-EU_0207/7; 0207/7
S1: 9077-2
SL1, SL2, SL3: M02S; 02P
SL4: M04; 04P
T1, T2: BD139; TO126

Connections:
+5V: D1.A, D1.C
GND: R1.1 (E), R2.1 (E), SL1.2, SL2.2, SL4.3, T1.1 (E), T2.1 (E)
GNDA: S1.2, SL3.1
unnamed: IC1.1 (OUT), R5.1
unnamed: IC1.3 (+IN), R1.2 (S)
unnamed: IC1.7 (OUT), R6.1
unnamed: IC1.5 (+IN), R2.2 (S)
unnamed: R5.2, T1.3 (B)
unnamed: R6.2, T2.3 (B)
unnamed: K1.1, K1.16 (2), SL1.1, T1.2 (C)
unnamed: S1.5, SL3.2
unnamed: K1.O2 (O), K1.S1 (S)
unnamed: K1.O1 (O), K1.S2 (S)
unnamed: K1.P1, P1.P1, S1.1 (S), S1.6 (O)
unnamed: K1.P2, P1.P2, S1.3 (O), S1.4 (S)
unnamed: P1.O2 (O), P1.S1 (S)
unnamed: P1.O1 (O), P1.S2 (S)
unnamed: IC1.2 (-IN), SL4.4
unnamed: IC1.6 (-IN), SL4.1
P1: P1.1, P1.16 (2), SL2.1, T2.2 (C)
V+: IC1.8 (V+)
V-: IC1.4 (V-)
VCC: R1.3 (A), R2.3 (A), SL4.2
